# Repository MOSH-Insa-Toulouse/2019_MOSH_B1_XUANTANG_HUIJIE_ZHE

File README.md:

# 2019_MOSH_B1_XUANTANG_HUIJIE_ZHE_MOHAN
This project aims to develop a dangerous gas detecting system, whose buzzer will alarm as soon as the gas index is higher than the warning line. The system includes programming the software based on Arduino, sending the data of gas sensor to TTN platform via LoRa, using Node-Red to display our data on a graphical interface and finally designing the PCB board by Kicad. 
 
 Documents in attachment
- Arduino Software files 
- Kicad files 
- Node-Red dashboard

## Arduino
Components:
- An Arduino uno board
- A Lora chip RN2483A
- A Grove Gas Sensor
- A buzzer

With Arduino, we achieve to make a detecting system that when the gas index is higher than our standard, the buzzer will alarm. We used interruption of arduino to do this. The code is in the folder.
After the soldering of the LoRa chip RN2483A, we succeed in communicating with the TTN platform, here is the screenshot of TTN:

Energy Consumption
To reduce the energy consumption, we decide to decrease the frequency of transmitting by sending data only when the gas index is higher than a seuil, otherwise, the LoRa system is in sleep mode. The energy consumption befor is 1.5W, and now the energy consumption reduced to 1.1W.

Node-Red
Finally, we did a dashboard by Node-Red, retrieving the data from TTN platform.

## kicad

In order to establish the best circuit between the LoRa module and the gas sensor introduced in the MOSH section above, we have drawn the following circuit diagram, which includes our components: a LoRa Module (RN2483) as transceiver, a Gas sensor, an amplifier (LTC1050) and two connector.

After the electrical diagram is completed, the different components must be packaged and integrated on a board. This is a complicated process, we have to consider the placement of components and the problem of circuit connection. The principle is to make the connection as simple as possible, without interleaving, and to ensure the safety of the circuit based on the correct circuit connection. Our results are as follows:

We have not only adjusted the layout of the components, but also considered the thickness and spacing of the connected copper wires, because copper wires that are too thin or too close will cause safety issues.

We used two layers of circuits, the lower layer was connected to ground, the voltage was zero. All the arrangements of wire are on the upper layer of the pcb board. If we need to connect to the ground, we will make a hole.
All the arrangements of wire are on the upper layer of the pcb board. If we need to connect to the ground, we will make a hole. The advantage of this method is that the upper circuit can be more concise.

Here is the final 3d model of our results:

## Part LTSpice

The stage is composed of several filters and an operational amplifier. We used LTSpice to simulate the analog circuit.

#### Question 1: check the operation in nominal conditions
Normally, the circuit amplify with a gain equals 100.
#### Question 2:  is the impact of the LTC1050C amplifier offset acceptable ?
The offset of input is 0.5mv, with our gain of 100, the offset of output 50mv which make 1 digit error in the 12 bits ADC.
#### Question 3:  is the impact of the amplifier input current acceptable ?
With the data sheet of ltc1050, we got the input noise current is 1.8fA/sqrt(HZ). So with a signal of 1KHz, we have an erreur 5.6E-14 << 1E-9 

#### Question 4:  what is the cutoff frequency of each low-pass filter stage?
stage 1: 15.9Hz
stage 2: 1.59Hz
stage 3: 1.59KHz
#### Question 5 : What is the global attenuation of a 50 Hz current noise ?
The global attenuation equals 40 dB of 50Hz current noise.

#### Question 6 : What is the global attenuation of a current noise occurring at the aliasing limit frequency (in the case of Arduino Uno ADC) ?
For a 16MHz Arduino, the ADC clock is set to 16MHz/128=125KHz. Each conversion takes 13 ADC clocks so 125KHz/13 = 9615Hz. At this frequency, we have an attenuation of 115 dB.

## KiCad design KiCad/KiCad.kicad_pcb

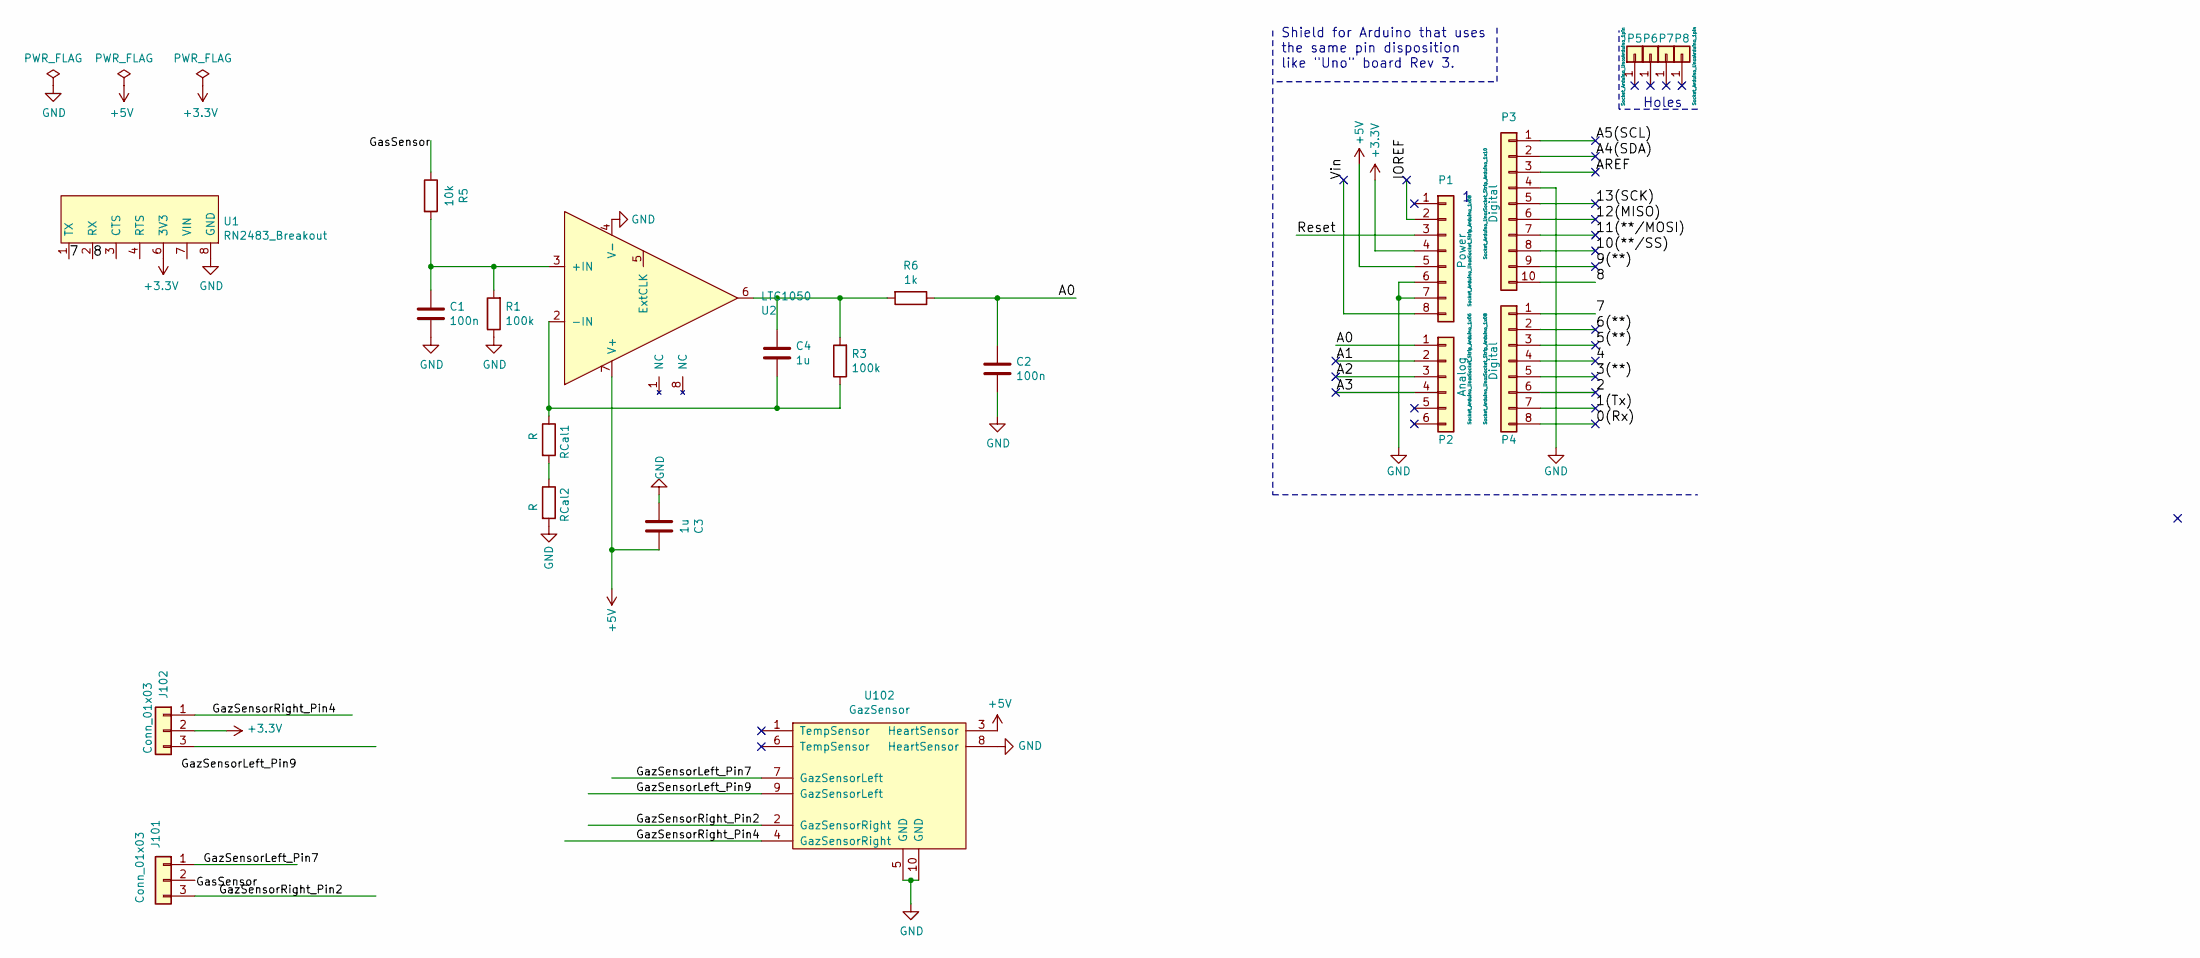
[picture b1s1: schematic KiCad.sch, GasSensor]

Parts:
C1, C2: 100n; CP_Radial_D4.0mm_P1.50mm
C3, C4: 1u; CP_Radial_D4.0mm_P1.50mm
J101, J102: Conn_01x03; PinHeader_1x03_P2.00mm_Vertical
P1: Power; Socket_Strip_Arduino_1x08
P2: Analog; Socket_Strip_Arduino_1x06
P3: Digital; Socket_Strip_Arduino_1x10
P4: Digital; Socket_Strip_Arduino_1x08
P5, P6, P7, P8: CONN_01X01; Arduino_1pin
R1, R3: 100k; R_Axial_DIN0207_L6.3mm_D2.5mm_P7.62mm_Horizontal
R5: 10k; R_Axial_DIN0207_L6.3mm_D2.5mm_P7.62mm_Horizontal
R6: 1k; R_Axial_DIN0207_L6.3mm_D2.5mm_P7.62mm_Horizontal
RCal1, RCal2: R; R_Axial_DIN0207_L6.3mm_D2.5mm_P7.62mm_Horizontal
U1: RN2483_Breakout
U2: LTC1050
U102: GazSensor; TO-5-10_Window

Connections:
+3V3: J102.2, P1.4, U1.6 (3V3)
+5V: C3.2, P1.5, U2.7 (V+), U102.3 (HeartSensor)
/0(Rx): P4.8
/1(Tx): P4.7
/2: P4.6
/3(**): P4.5
/4: P4.4
/5(**): P4.3
/6(**): P4.2
/7: P4.1, U1.1 (TX)
/8: P3.10, U1.2 (RX)
/9(**): P3.9
/10(**/SS): P3.8
/11(**/MOSI): P3.7
/12(MISO): P3.6
/13(SCK): P3.5
/A0: C2.1, P2.1, R6.1
/A1: P2.2
/A2: P2.3
/A3: P2.4
/A4(SDA): P3.2
/A5(SCL): P3.1
/AREF: P3.3
/GasSensor: R5.1
/GazSensorLeft_Pin7: J101.1, U102.7 (GazSensorLeft)
/GazSensorLeft_Pin9: U102.9 (GazSensorLeft)
/GazSensorRight_Pin2: J101.3, U102.2 (GazSensorRight)
/GazSensorRight_Pin4: J102.1, U102.4 (GazSensorRight)
/IOREF: P1.2
/Reset: P1.3
/Vin: P1.8
GND: C1.2, C2.2, C3.1, P1.6, P1.7, P3.4, R1.1, RCal2.2, U1.8 (GND), U2.4 (V-), U102.5 (GND), U102.8 (HeartSensor), U102.10 (GND)
unnamed: C1.1, R1.2, R5.2, U2.3 (+IN)
unnamed: C4.1, R3.2, R6.2, U2.6
unnamed: C4.2, R3.1, RCal1.1, U2.2 (-IN)
unnamed: RCal1.2, RCal2.1

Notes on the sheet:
Holes
Shield for Arduino that uses the same pin disposition like "Uno" board Rev 3.

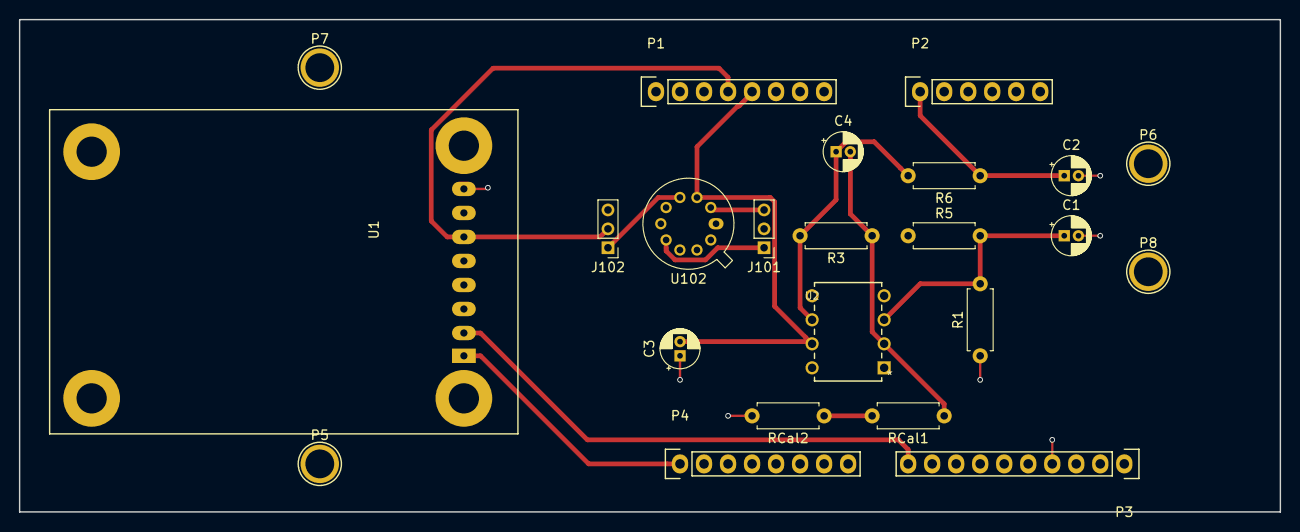
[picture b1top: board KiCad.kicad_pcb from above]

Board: 2 copper layers, 133.3 x 52.1 mm, 23 parts (0 on the bottom side), 13 nets.

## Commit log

2020-01-21 update image of ttn and arduino file
2020-01-21 update from QU
2020-01-22 update Ltspice part
2020-01-27 data sheet
